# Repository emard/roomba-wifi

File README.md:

# WiFi-Roomba: ESP8266 Nodemcu interface for iRobot Roomba

Wifi remote control interface for the iRobot Roomba vacuum cleaner.
Tested on model 880, others 600-900 have similar command
set and probably will work too.

telnet to roomba IP while it is charging, it should display something like this:

    telnet 192.168.0.2
    Trying 192.168.0.2...
    Connected to 192.168.0.2.
    Escape character is '^]'.
    bat:   min 0  sec 10  mV 17061  mA 1016  tenths-deg-C 348  mAH 2696  state 5  
    bat:   min 0  sec 11  mV 17061  mA 1016  tenths-deg-C 348  mAH 2696  state 5  
    bat:   min 0  sec 12  mV 17061  mA 1008  tenths-deg-C 348  mAH 2696  state 5  
    bat:   min 0  sec 13  mV 17061  mA 1023  tenths-deg-C 348  mAH 2696  state 5  

To reset roomba to similar state like battery was replaced,
type CTRL-G and ENTER. Roomba beeps and prints different
messages after reset and again battery charging messages as above.

to exit telnet, type CTRL-] quit ENTER

    ^]
    telnet> quit

python3 script to send "DOCK" command

    #!/usr/bin/env python3
    import socket
    s = socket.socket(socket.AF_INET, socket.SOCK_STREAM)
    s.connect(("192.168.0.2",23))
    #print(s.recv(256))
    #s.send(bytearray([128, 135, 173])) # start, clean, stop
    s.send(bytearray([128, 143, 173])) # start, seek dock, stop
    s.close()

python3 script to shown 4 chars approximated on 7-segment display:

    #!/usr/bin/env python3
    import socket, sys, time
    disp = sys.argv[1][0:4].encode() # max 4 chars
    disp += b" " * (4-len(disp)) # pad length 4 with spaces
    s = socket.socket(socket.AF_INET, socket.SOCK_STREAM)
    s.connect(("192.168.48.116",23))
    s.send(bytearray([128, 131, 174])) # safe mode
    time.sleep(0.05)
    s.send(bytearray([164])+disp)
    s.close()

    ./roomba.disp.py TEST

Other commands are described in
[iRobot Roomba 600 Open Interface Spec](https://www.irobotweb.com/-/media/MainSite/PDFs/About/STEM/Create/iRobot_Roomba_600_Open_Interface_Spec.pdf)

# Wifi Module

Get nodemcu from ebay for $3.5 and flash it with some TCP-serial
bridge code.

From Arduino install ESP8266 support from Boards Manager.

set board to "NodeMCU 1.0 (ESP-12E Module)".

open Examples -> ESP8266Wifi ->  WifiTelnetToSerial

setup WiFi user and password to connect to local access 
point and enable "SWAP_PINS" to use hardware serial 115200,8,n,1
connected as RX=gpio13, TX=gpio15 to Roomba:

    #define SWAP_PINS 1

To compile and write flash, click round blue button with right arrow.

When monitored at USB-serial port, it will print IP address where it
connected.

# Power supply

Get 3.3V switching power supply module from ebay for $2:

    2A DC 5V-23V to 3.3V DC-DC Step-Down Power Supply Buck Module for esp8266 WiFi

On the back of the module PCB is written:

       Canton-Power
          DC-DC
    Step-Down Converter
    3.3V[x] 5V[ ] Vi GND Vo

# Cable

Adafruit has roomba cable.
Also apple or mac 8-pin mini-din cable ordered from ebay
will fit to roomba socket (it has extra middle pin which
is NC in roomba socket).

pinout (wire colors inside of apple cable)

    1  Vpwr   red    ? no voltage
    2  Vpwr   brown  20V
    3  RXD    orange input to roomba 5V TTL <- wifi_gpio15
    4  TXD    black  output from roomba 5V TTL -> wifi_gpio13
    5  DD     yellow wifi_gpio12
    6  GND    green
    7  GND    blue
    8  NC     violet (middle pin)
    SHIELD    naked

same pin numbering to DB9 connector

# PCB

You can order from OSHpark, seeedstudio or similar, email them gerber
files and they will send back the PCB:

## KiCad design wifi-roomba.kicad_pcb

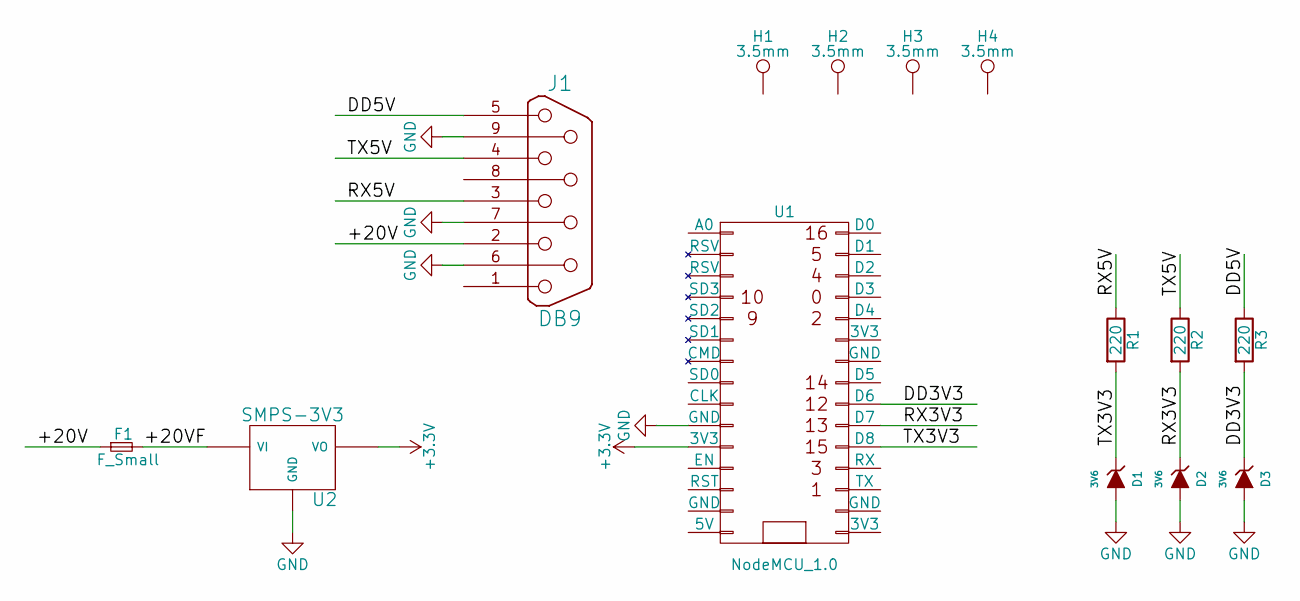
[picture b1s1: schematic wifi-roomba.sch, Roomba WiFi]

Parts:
D1, D2, D3: 3V6; SMD-1206_Pol
F1: F_Small; Fuseholder5x20_horiz_SemiClosed_Casing10x25mm
H1, H2, H3, H4: 3.5mm; MountingHole_3.5mm_Pad
J1: DB9; DB9FC
R1, R2, R3: 220; R_1206
U1: NodeMCU_1.0
U2: SMPS-3V3; PINHEAD1-3

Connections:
+3V3: U1.11 (3V3), U2.VO
/+20V: F1.1, J1.2
/+20VF: F1.2, U2.VI
/DD3V3: D3.1 (K), R3.2, U1.22 (D6)
/DD5V: J1.5, R3.1
/RX3V3: D2.1 (K), R2.2, U1.21 (D7)
/RX5V: J1.3, R1.1
/TX3V3: D1.1 (K), R1.2, U1.20 (D8)
/TX5V: J1.4, R2.1
GND: D1.2 (A), D2.2 (A), D3.2 (A), J1.6, J1.7, J1.9, U1.10 (GND), U2.GND

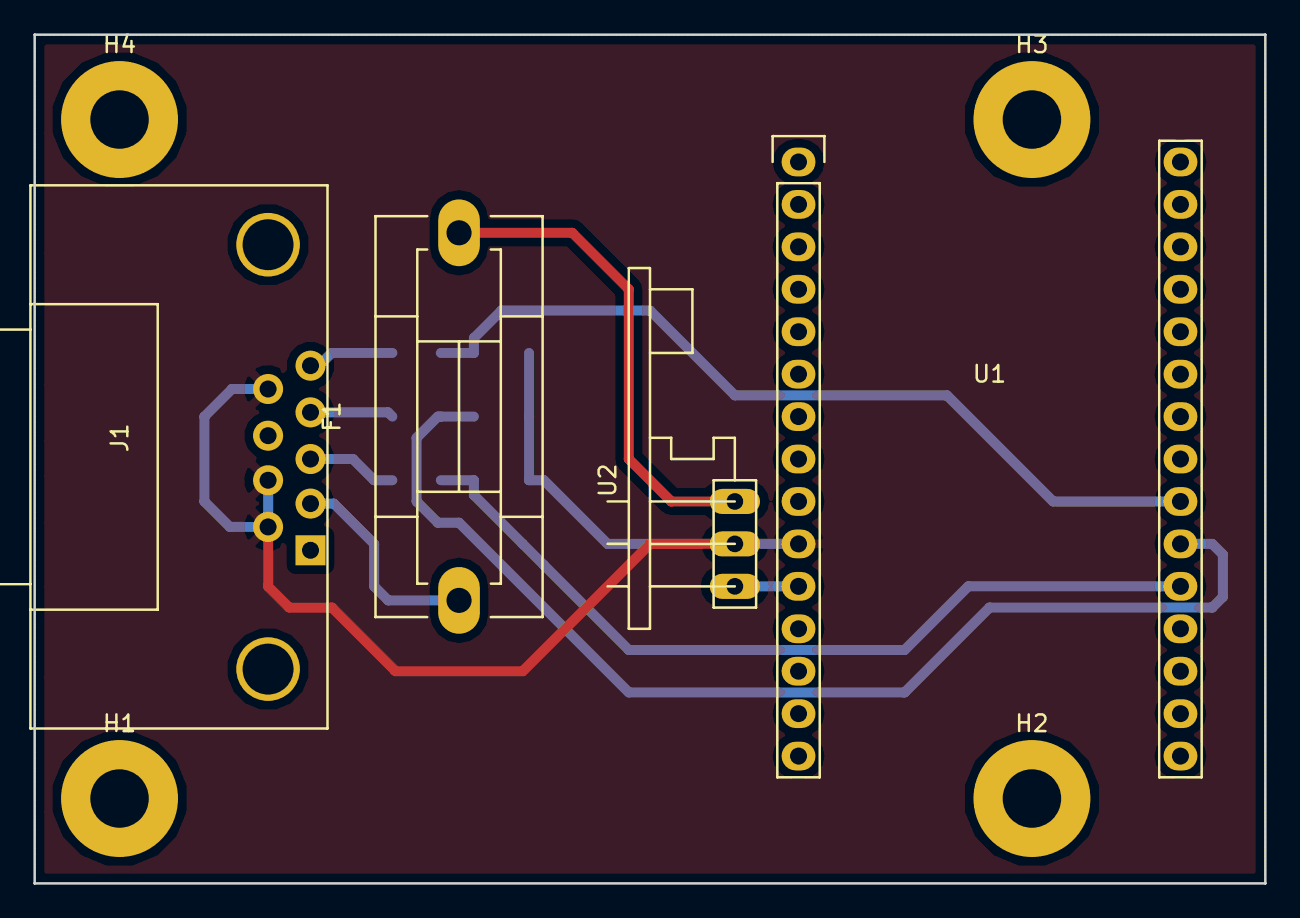
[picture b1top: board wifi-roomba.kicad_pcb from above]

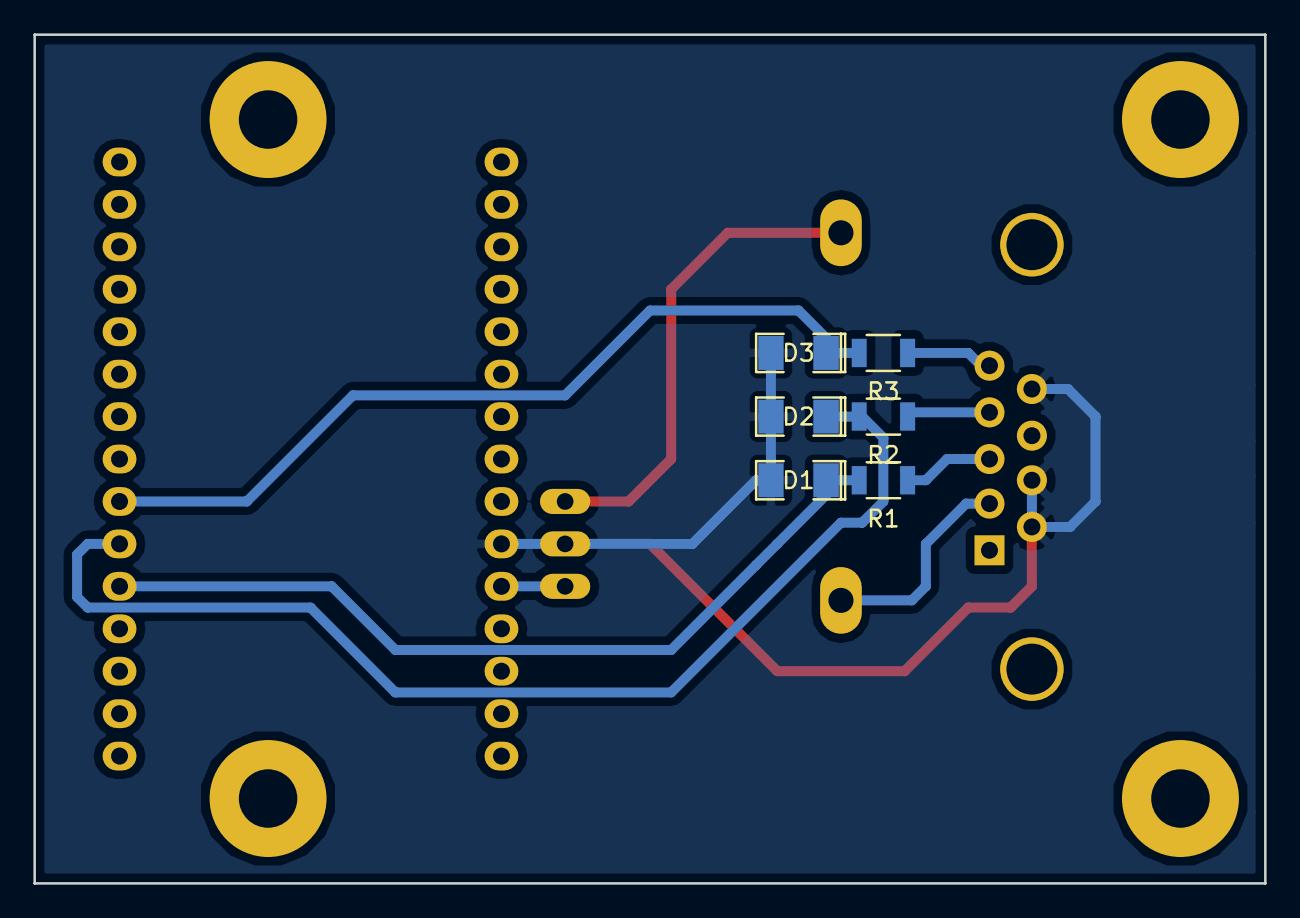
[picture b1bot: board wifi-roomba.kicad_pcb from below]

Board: 2 copper layers, 73.7 x 50.8 mm, 14 parts (6 on the bottom side), 10 nets.

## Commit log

2017-04-17 3D view picture
2017-04-17 readme cable pinout
2017-04-17 typo
2017-04-17 readme update, power supply order details
2017-04-17 readme update
2017-04-17 dcdc converter picture
2017-04-17 nodemcu picture
2021-11-28 wifi pins connected
2021-11-28 schematics pdf
2021-11-29 pins typo
2021-11-29 pins
2021-11-29 readme what should be printed and how to reset roomba
2021-11-29 spec pdf
2021-11-29 readme
2021-11-29 readme compiling
2021-11-29 swap serial better description
2021-11-29 baudate
2021-11-29 python example
2021-11-29 readme simplify
2021-11-29 readme dock
2021-11-30 few python scripts
2021-11-30 script to show text on 7-segment display
2021-11-30 fix disp script
2021-11-30 small comment
2021-12-01 script to set time
2021-12-01 one script with multiple functions
2021-12-01 btn pressing
2021-12-01 improve clock setting
2021-12-01 update script to always stop
